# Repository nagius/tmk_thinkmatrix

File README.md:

# ThinkMatrix Keyboard Firmware

This is the firmware for my custom ortholinear keyboard, based on the [tmk keyboard library](https://github.com/tmk/tmk_core).  

The keyboard runs on a [Teensy 2.0](http://www.pjrc.com/store/teensy.html). You can find more detail about the design of keyboard itself in the directory `docs`.

Images and a buildlog of the keyboard can be found [here](https://geekhack.org/index.php?topic=76167.0).

## Cloning, building & flashing

You need the AVR cross-compilation toolstack to compile the firmware.

See [tmk keyboard](https://github.com/tmk/tmk_keyboard) and [Teensy howto](https://www.pjrc.com/teensy/gcc.html) for more informations.

Since this repository has a submodule the cloning needs an additional argument to init and update the submodule.

```
git clone --recursive https://github.com/nagius/tmk_thinkmatrix
cd tmk_thinkmatrix
make
```

This will generate the firmware file `thinkmatrix-fw.hex`.

### Upload

Start the graphical [loader tool](https://www.pjrc.com/teensy/loader_linux.html) :

```
teensy.64bit &
```

Plug the Teensy on USB, push the program button, select the generated file `thinkmatrix-fw.hex` and click 'Upload'.

## Update to the lastest version

```
git pull
git submodule sync --recursive
git submodule update --init --recursive
```

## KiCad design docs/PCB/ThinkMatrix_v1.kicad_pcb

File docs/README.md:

# Documentation, schematics and drawing

You will find in this directory the files needed to buid the keyboard. Everything is released under GNU/GPLv3 Licence if not specified otherwise.
 
 - keyboard-layout.json: Data file for http://www.keyboard-layout-editor.com/
 - CAD: All LibreCAD needed to build the case and the plate
 - PCB: the KiCad project to make the PCB

Please note there is a couple of errors on this PCB design:

 - The pins labelling of the Teensy module are wrong, please refer to the table below for the correct pinout.
 - When soldering the Teensy, pins C6 and D7 must be swapped (with a couple of wire for example).
 - Clearance around the Cherry MX stabilizers is not good enough in few cases, 5 of the resistors need to be soldiered on the back of the board.
 - The diodes are in the wrong way around for the tmk_keyboard firmware, the matrix need to be rotated in the source code. Note this is tmk specific, it does not apply if you're using a qmk_keyboard firmware.

## Teensy pinout

 - Matrix

| Row | 0  | 1  | 2  | 3  | 4  | 5  | 6  |
|-----|----|----|----|----|----|----|----|
| Pin | B2 | B0 | B1 | E6 | B3 | B7 | D0 |

| Col | 0  | 1  | 2  | 3  | 4  | 5  | 6  | 7  | 8  | 9  | 10 | 11 | 12 | 13 |
|-----|----|----|----|----|----|----|----|----|----|----|----|----|----|----|
| Pin | F0 | F1 | F4 | B4 | F5 | D3 | D2 | C7 | F7 | B6 | B5 | D5 | D4 | C6 |

 - Front leds: D1, D6, F6
 - Backlight: D7

## Parts list

 - 1x  Teensy 2.0
 - 85x Cherry MX switches
 - 9x  Cherry MX stabilizers
 - 85x Diodes 1N4148
 - 89x Orange LEDs (1.92V @ 7mA)
 - 43x Resistors 36 ohms
 - 4x  Resistors 200 ohms
 - 1x  Resistor 1.4k ohms
 - 1x  Capacitor 100µF
 - 1x  Transistor 2N3904
 - 1x  Transistor PN2907A

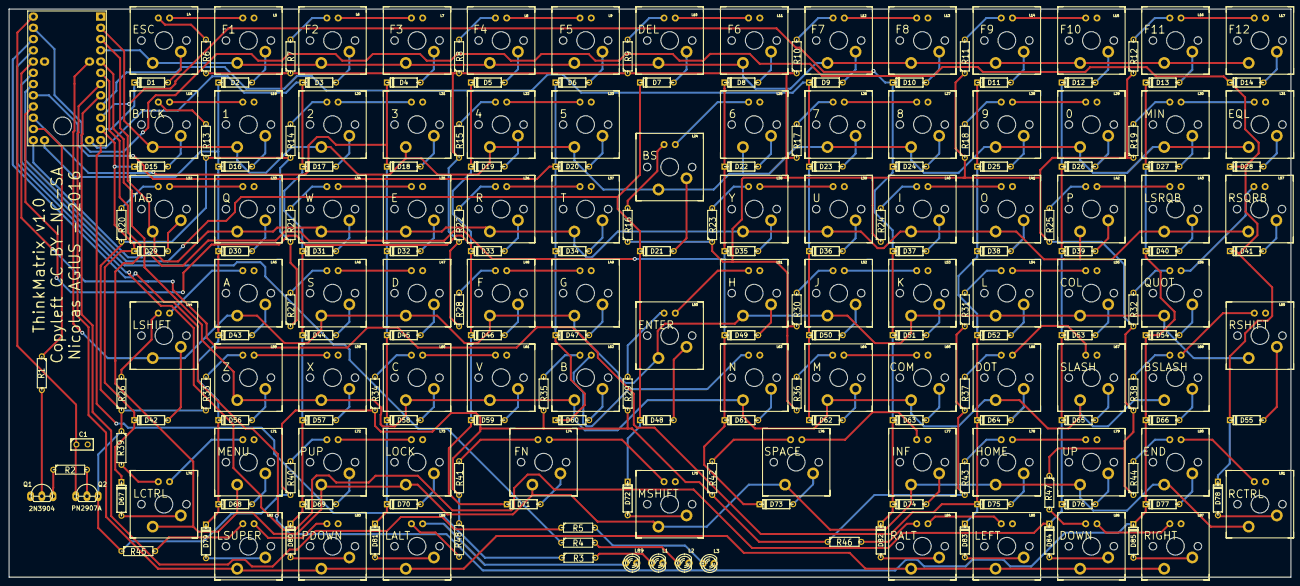
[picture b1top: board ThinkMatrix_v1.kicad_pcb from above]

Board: 2 copper layers, 289.7 x 128.4 mm, 311 parts (0 on the bottom side), 205 nets.

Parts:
C1: 47µF; C1
D1, D2, D3, D4, D5, D6, D7, D8, D9, D10, D11, D12, D13, D14, D15, D16, D17, D18, D19, D20, D21, D22, D23, D24, D25, D26, D27, D28, D29, D30, D31, D32, D33, D34, D35, D36, D37, D38, D39, D40, D41, D42, D43, D44, D45, D46, D47, D48, D49, D50, D51, D52, D53, D54, D55, D56, D57, D58, D59, D60, D61, D62, D63, D64, D65, D66, D67, D68, D69, D70, D71, D72, D73, D74, D75, D76, D77, D78, D79, D80, D81, D82, D83, D84, D85: DIODE; D3
L1, L2, L3, L89: LED-3MM
L4: L4; MX1A-led-rev
L5: L5; MX1A-led-rev
L6: L6; MX1A-led-rev
L7: L7; MX1A-led-rev
L8: L8; MX1A-led-rev
L9: L9; MX1A-led-rev
L10: L10; MX1A-led-rev
L11: L11; MX1A-led-rev
L12: L12; MX1A-led-rev
L13: L13; MX1A-led-rev
L14: L14; MX1A-led-rev
L15: L15; MX1A-led-rev
L16: L16; MX1A-led-rev
L17: L17; MX1A-led-rev
L18: L18; MX1A-led-rev
L19: L19; MX1A-led-rev
L20: L20; MX1A-led-rev
L21: L21; MX1A-led-rev
L22: L22; MX1A-led-rev
L23: L23; MX1A-led-rev
L24: L24; MX1A-led-rev
L25: L25; MX1A-led-rev
L26: L26; MX1A-led-rev
L27: L27; MX1A-led-rev
L28: L28; MX1A-led-rev
L29: L29; MX1A-led-rev
L30: L30; MX1A-led-rev
L31: L31; MX1A-led-rev
L32: L32; MX1A-led-rev
L33: L33; MX1A-led-rev
L34: L34; MX1A-led-rev
L35: L35; MX1A-led-rev
L36: L36; MX1A-led-rev
L37: L37; MX1A-led-rev
L38: L38; MX1A-led-rev
L39: L39; MX1A-led-rev
L40: L40; MX1A-led-rev
L41: L41; MX1A-led-rev
L42: L42; MX1A-led-rev
L43: L43; MX1A-led-rev
L44: L44; MX1A-led-rev
L45: L45; MX1A-led-rev
L46: L46; MX1A-led-rev
L47: L47; MX1A-led-rev
L48: L48; MX1A-led-rev
L49: L49; MX1A-led-rev
L50: L50; MX1A-led-rev
L51: L51; MX1A-led-rev
L52: L52; MX1A-led-rev
L53: L53; MX1A-led-rev
L54: L54; MX1A-led-rev
L55: L55; MX1A-led-rev
L56: L56; MX1A-led-rev
L57: L57; MX1A-led-rev
L58: L58; MX1A-led-rev
L59: L59; MX1A-led-rev
L60: L60; MX1A-led-rev
L61: L61; MX1A-led-rev
L62: L62; MX1A-led-rev
L63: L63; MX1A-led-rev
L64: L64; MX1A-led-rev
L65: L65; MX1A-led-rev
L66: L66; MX1A-led-rev
L67: L67; MX1A-led-rev
L68: L68; MX1A-led-rev
L69: L69; MX1A-led-rev
L70: L70; MX1A-led-rev
L71: L71; MX1A-led-rev
L72: L72; MX1A-led-rev
L73: L73; MX1A-led-rev
L74: L74; MX1A-led-rev
L75: L75; MX1A-led-rev
L76: L76; MX1A-led-rev
L77: L77; MX1A-led-rev
L78: L78; MX1A-led-rev
L79: L79; MX1A-led-rev
L80: L80; MX1A-led-rev
L81: L81; MX1A-led-rev
L82: L82; MX1A-led-rev
L83: L83; MX1A-led-rev
L84: L84; MX1A-led-rev
L85: L85; MX1A-led-rev
L86: L86; MX1A-led-rev
L87: L87; MX1A-led-rev
L88: L88; MX1A-led-rev
Q1: 2N3904; LV_TO92-123_oval
Q2: PN2907A; LV_TO92-123_oval
R1: R1; R3
R2: R2; R3
R3: R3
R4: R4; R3
R5: R5; R3
R6: R6; R3
R7: R7; R3
R8: R8; R3
R9: R9; R3
R10: R10; R3
R11: R11; R3
R12: R12; R3
R13: R13; R3
R14: R14; R3
R15: R15; R3
R16: R16; R3
R17: R17; R3
R18: R18; R3
R19: R19; R3
R20: R20; R3
R21: R21; R3
R22: R22; R3
R23: R23; R3
R24: R24; R3
R25: R25; R3
R26: R26; R3
R27: R27; R3
R28: R28; R3
R29: R29; R3
R30: R30; R3
R31: R31; R3
R32: R32; R3
R33: R33; R3
R34: R34; R3
R35: R35; R3
R36: R36; R3
R37: R37; R3
R38: R38; R3
R39: R39; R3
R40: R40; R3
R41: R41; R3
R42: R42; R3
R43: R43; R3
R44: R44; R3
R45: R45; R3
R46: R46; R3
R47: R47; R3
R48: R48; R3
SW0:0: ESC; SW_PCB_2PIN_NO
SW0:1: F1; SW_PCB_2PIN_NO
SW0:2: F2; SW_PCB_2PIN_NO
SW0:3: F3; SW_PCB_2PIN_NO
SW0:4: F4; SW_PCB_2PIN_NO
SW0:5: F5; SW_PCB_2PIN_NO
SW0:6: DEL; SW_PCB_2PIN_NO
SW0:7: F6; SW_PCB_2PIN_NO
SW0:8: F7; SW_PCB_2PIN_NO
SW0:9: F8; SW_PCB_2PIN_NO
SW0:10: F9; SW_PCB_2PIN_NO
SW0:11: F10; SW_PCB_2PIN_NO
SW0:12: F11; SW_PCB_2PIN_NO
SW0:13: F12; SW_PCB_2PIN_NO
SW1:0: BTICK; SW_PCB_2PIN_NO
SW1:1: 1; SW_PCB_2PIN_NO
SW1:2: 2; SW_PCB_2PIN_NO
SW1:3: 3; SW_PCB_2PIN_NO
SW1:4: 4; SW_PCB_2PIN_NO
SW1:5: 5; SW_PCB_2PIN_NO
SW1:6: BS; SW_PCB_2PIN_NO
SW1:7: 6; SW_PCB_2PIN_NO
SW1:8: 7; SW_PCB_2PIN_NO
SW1:9: 8; SW_PCB_2PIN_NO
SW1:10: 9; SW_PCB_2PIN_NO
SW1:11: 0; SW_PCB_2PIN_NO
SW1:12: MIN; SW_PCB_2PIN_NO
SW1:13: EQL; SW_PCB_2PIN_NO
SW2:0: TAB; SW_PCB_2PIN_NO
SW2:1: Q; SW_PCB_2PIN_NO
SW2:2: W; SW_PCB_2PIN_NO
SW2:3: E; SW_PCB_2PIN_NO
SW2:4: R; SW_PCB_2PIN_NO
SW2:5: T; SW_PCB_2PIN_NO
SW2:7: Y; SW_PCB_2PIN_NO
SW2:8: U; SW_PCB_2PIN_NO
SW2:9: I; SW_PCB_2PIN_NO
SW2:10: O; SW_PCB_2PIN_NO
SW2:11: P; SW_PCB_2PIN_NO
SW2:12: LSRQB; SW_PCB_2PIN_NO
SW2:13: RSQRB; SW_PCB_2PIN_NO
SW3:0: LSHIFT; SW_PCB_2PIN_NO
SW3:1: A; SW_PCB_2PIN_NO
SW3:2: S; SW_PCB_2PIN_NO
SW3:3: D; SW_PCB_2PIN_NO
SW3:4: F; SW_PCB_2PIN_NO
SW3:5: G; SW_PCB_2PIN_NO
SW3:6: ENTER; SW_PCB_2PIN_NO
SW3:7: H; SW_PCB_2PIN_NO
SW3:8: J; SW_PCB_2PIN_NO
SW3:9: K; SW_PCB_2PIN_NO
SW3:10: L; SW_PCB_2PIN_NO
SW3:11: COL; SW_PCB_2PIN_NO
SW3:12: QUOT; SW_PCB_2PIN_NO
SW3:13: RSHIFT; SW_PCB_2PIN_NO
SW4:1: Z; SW_PCB_2PIN_NO
SW4:2: X; SW_PCB_2PIN_NO
SW4:3: C; SW_PCB_2PIN_NO
SW4:4: V; SW_PCB_2PIN_NO
SW4:5: B; SW_PCB_2PIN_NO
SW4:7: N; SW_PCB_2PIN_NO
SW4:8: M; SW_PCB_2PIN_NO
SW4:9: COM; SW_PCB_2PIN_NO
SW4:10: DOT; SW_PCB_2PIN_NO
SW4:11: SLASH; SW_PCB_2PIN_NO
SW4:12: BSLASH; SW_PCB_2PIN_NO
SW5:0: LCTRL; SW_PCB_2PIN_NO
SW5:1: MENU; SW_PCB_2PIN_NO
SW5:2: PUP; SW_PCB_2PIN_NO
SW5:3: LOCK; SW_PCB_2PIN_NO
SW5:4: FN; SW_PCB_2PIN_NO
SW5:6: MSHIFT; SW_PCB_2PIN_NO
SW5:7: SPACE; SW_PCB_2PIN_NO
SW5:9: INF; SW_PCB_2PIN_NO
SW5:10: HOME; SW_PCB_2PIN_NO
SW5:11: UP; SW_PCB_2PIN_NO
SW5:12: END; SW_PCB_2PIN_NO
SW5:13: RCTRL; SW_PCB_2PIN_NO
SW6:1: LSUPER; SW_PCB_2PIN_NO
SW6:2: PDOWN; SW_PCB_2PIN_NO
SW6:3: LALT; SW_PCB_2PIN_NO
SW6:9: RALT; SW_PCB_2PIN_NO
SW6:10: LEFT; SW_PCB_2PIN_NO
SW6:11: DOWN; SW_PCB_2PIN_NO
SW6:12: RIGHT; SW_PCB_2PIN_NO
U1: TEENSY2.0; TEENSY_2.0_rev

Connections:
GND: C1.2, L1.2, L2.2, L3.2, L5.2, L7.2, L9.2, L11.2, L13.2, L15.2, L17.2, L19.2, L21.2, L23.2, L25.2, L27.2, L29.2, L31.2, L33.2, L35.2, L37.2, L39.2, L41.2, L43.2, L45.2, L47.2, L49.2, L51.2, L53.2, L55.2, L57.2, L59.2, L61.2, L63.2, L65.2, L67.2, L69.2, L71.2, L73.2, L75.2, L77.2, L79.2, L81.2, L83.2, L85.2, L87.2, L89.2, Q1.1, U1.1
unnamed: L34.1, R21.2
unnamed: L36.1, R22.2
unnamed: L36.2, L37.1
unnamed: L34.2, L35.1
unnamed: L32.2, L33.1
unnamed: L32.1, R20.2
unnamed: L38.1, R23.2
unnamed: L40.1, R24.2
unnamed: L40.2, L41.1
unnamed: L38.2, L39.1
unnamed: L28.1, R18.2
unnamed: L28.2, L29.1
unnamed: L26.2, L27.1
unnamed: L26.1, R17.2
unnamed: L24.2, L25.1
unnamed: L24.1, R16.2
unnamed: L30.2, L31.1
unnamed: L30.1, R19.2
unnamed: L52.1, R30.2
unnamed: L54.1, R31.2
unnamed: L52.2, L53.1
unnamed: L54.2, L55.1
unnamed: L50.2, L51.1
unnamed: L50.1, R29.2
unnamed: L56.2, L57.1
unnamed: L58.1, R33.2
unnamed: L58.2, L59.1
unnamed: L56.1, R32.2
unnamed: L44.2, L45.1
unnamed: L44.1, R26.2
unnamed: L46.2, L47.1
unnamed: L42.2, L43.1
unnamed: L42.1, R25.2
unnamed: L48.2, L49.1
unnamed: L48.1, R28.2
unnamed: L46.1, R27.2
unnamed: R1.1, U1.19
unnamed: Q1.3, R2.1
unnamed: Q2.2, R2.2
unnamed: Q1.2, R1.2
unnamed: L6.1, R7.2
unnamed: L6.2, L7.1
unnamed: R4.1, U1.24
unnamed: R5.1, U1.8
unnamed: R3.1, U1.12
unnamed: L4.2, L5.1
unnamed: L20.2, L21.1
unnamed: L18.2, L19.1
unnamed: L18.1, R13.2
unnamed: L20.1, R14.2
unnamed: L16.2, L17.1
unnamed: L16.1, R12.2
unnamed: L22.1, R15.2
unnamed: L22.2, L23.1
unnamed: L8.2, L9.1
unnamed: L10.2, L11.1
unnamed: L10.1, R9.2
unnamed: L8.1, R8.2
unnamed: L14.2, L15.1
unnamed: L14.1, R11.2
unnamed: L12.2, L13.1
unnamed: L12.1, R10.2
unnamed: SW2:0.1, SW2:1.1, SW2:2.1, SW2:3.1, SW2:4.1, SW2:5.1, SW2:7.1, SW2:8.1, SW2:9.1, SW2:10.1, SW2:11.1, SW2:12.1, SW2:13.1, U1.3
unnamed: D12.2, D26.2, D39.2, D53.2, D65.2, D76.2, D84.2, U1.26
unnamed: L68.1, R38.2
unnamed: L70.1, R39.2
unnamed: L70.2, L71.1
unnamed: L68.2, L69.1
unnamed: L66.2, L67.1
unnamed: L66.1, R37.2
unnamed: L72.2, L73.1
unnamed: L74.2, L75.1
unnamed: L74.1, R41.2
unnamed: L72.1, R40.2
unnamed: L62.1, R35.2
unnamed: L62.2, L63.1
unnamed: L60.2, L61.1
unnamed: L60.1, R34.2
unnamed: L64.2, L65.1
unnamed: L64.1, R36.2
unnamed: L86.1, R47.2
unnamed: L88.1, R48.2
unnamed: L86.2, L87.1
unnamed: L88.2, L89.1
unnamed: L84.2, L85.1
unnamed: L84.1, R46.2
unnamed: D1.2, D15.2, D29.2, D42.2, D67.2, U1.11
unnamed: D6.2, D20.2, D34.2, D47.2, D60.2, U1.22
unnamed: D7.2, D21.2, D48.2, D72.2, U1.23
unnamed: L78.2, L79.1
unnamed: L78.1, R43.2
unnamed: L80.2, L81.1
unnamed: L76.2, L77.1
unnamed: L76.1, R42.2
unnamed: L82.2, L83.1
unnamed: L82.1, R45.2
unnamed: L4.1, R6.2
unnamed: L80.1, R44.2
unnamed: Q2.3, R6.1, R7.1, R8.1, R9.1, R10.1, R11.1, R12.1, R13.1, R14.1, R15.1, R16.1, R17.1, R18.1, R19.1, R20.1, R21.1, R22.1, R23.1, R24.1, R25.1, R26.1, R27.1, R28.1, R29.1, R30.1, R31.1, R32.1, R33.1, R34.1, R35.1, R36.1, R37.1, R38.1, R39.1, R40.1, R41.1, R42.1, R43.1, R44.1, R45.1, R46.1, R47.1, R48.1
unnamed: D46.1, SW3:4.2
unnamed: D33.1, SW2:4.2
unnamed: D5.2, D19.2, D33.2, D46.2, D59.2, D71.2, U1.21
unnamed: D19.1, SW1:4.2
unnamed: D4.1, SW0:3.2
unnamed: D71.1, SW5:4.2
unnamed: D59.1, SW4:4.2
unnamed: D4.2, D18.2, D32.2, D45.2, D58.2, D70.2, D81.2, U1.20
unnamed: D58.1, SW4:3.2
unnamed: D45.1, SW3:3.2
unnamed: D32.1, SW2:3.2
unnamed: D18.1, SW1:3.2
unnamed: D81.1, SW6:3.2
unnamed: D5.1, SW0:4.2
unnamed: D70.1, SW5:3.2
unnamed: D48.1, SW3:6.2
unnamed: D72.1, SW5:6.2
unnamed: D21.1, SW1:6.2
unnamed: D35.1, SW2:7.2
unnamed: D22.1, SW1:7.2
unnamed: D7.1, SW0:6.2
unnamed: D20.1, SW1:5.2
unnamed: D34.1, SW2:5.2
unnamed: D60.1, SW4:5.2
unnamed: D6.1, SW0:5.2
unnamed: D47.1, SW3:5.2
unnamed: D67.1, SW5:0.2
unnamed: D1.1, SW0:0.2
unnamed: SW1:0.1, SW1:1.1, SW1:2.1, SW1:3.1, SW1:4.1, SW1:5.1, SW1:6.1, SW1:7.1, SW1:8.1, SW1:9.1, SW1:10.1, SW1:11.1, SW1:12.1, SW1:13.1, U1.2
unnamed: D42.1, SW3:0.2
unnamed: D43.1, SW3:1.2
unnamed: D30.1, SW2:1.2
unnamed: D16.1, SW1:1.2
unnamed: D15.1, SW1:0.2
unnamed: D29.1, SW2:0.2
unnamed: C1.1, Q2.1, U1.29
unnamed: D3.2, D17.2, D31.2, D44.2, D57.2, D69.2, D80.2, U1.13
unnamed: D69.1, SW5:2.2
unnamed: D57.1, SW4:2.2
unnamed: D44.1, SW3:2.2
unnamed: D3.1, SW0:2.2
unnamed: D31.1, SW2:2.2
unnamed: D80.1, SW6:2.2
unnamed: D68.1, SW5:1.2
unnamed: D79.1, SW6:1.2
unnamed: D2.2, D16.2, D30.2, D43.2, D56.2, D68.2, D79.2, U1.17
unnamed: D56.1, SW4:1.2
unnamed: D17.1, SW1:2.2
unnamed: D2.1, SW0:1.2
unnamed: D27.1, SW1:12.2
unnamed: D40.1, SW2:12.2
unnamed: D12.1, SW0:11.2
unnamed: D66.1, SW4:12.2
unnamed: D77.1, SW5:12.2
unnamed: D54.1, SW3:12.2
unnamed: SW4:1.1, SW4:2.1, SW4:3.1, SW4:4.1, SW4:5.1, SW4:7.1, SW4:8.1, SW4:9.1, SW4:10.1, SW4:11.1, SW4:12.1, U1.5
unnamed: D53.1, SW3:11.2
unnamed: D65.1, SW4:11.2
unnamed: D39.1, SW2:11.2
unnamed: D26.1, SW1:11.2
unnamed: D76.1, SW5:11.2
unnamed: D84.1, SW6:11.2
unnamed: L1.1, R3.2
unnamed: L2.1, R4.2
unnamed: D14.1, SW0:13.2
unnamed: L3.1, R5.2
unnamed: D13.2, D27.2, D40.2, D54.2, D66.2, D77.2, D85.2, U1.27
unnamed: D28.1, SW1:13.2
unnamed: D14.2, D28.2, D41.2, D55.2, D78.2, U1.28
unnamed: D13.1, SW0:12.2
unnamed: D85.1, SW6:12.2
unnamed: D55.1, SW3:13.2
unnamed: D78.1, SW5:13.2
unnamed: D41.1, SW2:13.2
unnamed: D62.1, SW4:8.2
unnamed: D9.1, SW0:8.2
unnamed: D9.2, D23.2, D36.2, D50.2, D62.2, U1.9
unnamed: SW0:0.1, SW0:1.1, SW0:2.1, SW0:3.1, SW0:4.1, SW0:5.1, SW0:6.1, SW0:7.1, SW0:8.1, SW0:9.1, SW0:10.1, SW0:11.1, SW0:12.1, SW0:13.1, U1.4
unnamed: D50.1, SW3:8.2
unnamed: D51.1, SW3:9.2
unnamed: SW3:0.1, SW3:1.1, SW3:2.1, SW3:3.1, SW3:4.1, SW3:5.1, SW3:6.1, SW3:7.1, SW3:8.1, SW3:9.1, SW3:10.1, SW3:11.1, SW3:12.1, SW3:13.1, U1.31
unnamed: D37.1, SW2:9.2
unnamed: D24.1, SW1:9.2
unnamed: D73.1, SW5:7.2
unnamed: D8.2, D22.2, D35.2, D49.2, D61.2, D73.2, U1.18
unnamed: D61.1, SW4:7.2
unnamed: D49.1, SW3:7.2
unnamed: D23.1, SW1:8.2
unnamed: D36.1, SW2:8.2
unnamed: D8.1, SW0:7.2
unnamed: D75.1, SW5:10.2
unnamed: D64.1, SW4:10.2
unnamed: D11.2, D25.2, D38.2, D52.2, D64.2, D75.2, D83.2, U1.25
unnamed: D52.1, SW3:10.2
unnamed: D38.1, SW2:10.2
unnamed: D11.1, SW0:10.2
unnamed: D83.1, SW6:10.2
unnamed: SW5:0.1, SW5:1.1, SW5:2.1, SW5:3.1, SW5:4.1, SW5:6.1, SW5:7.1, SW5:9.1, SW5:10.1, SW5:11.1, SW5:12.1, SW5:13.1, U1.6
unnamed: D10.2, D24.2, D37.2, D51.2, D63.2, D74.2, D82.2, U1.10
unnamed: D82.1, SW6:9.2
unnamed: SW6:1.1, SW6:2.1, SW6:3.1, SW6:9.1, SW6:10.1, SW6:11.1, SW6:12.1, U1.7
unnamed: D74.1, SW5:9.2
unnamed: D63.1, SW4:9.2
unnamed: D25.1, SW1:10.2
unnamed: D10.1, SW0:9.2

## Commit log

2016-10-15 Added tmk_core submodule
2016-10-15 Added source code
2016-10-15 Added comments
2016-10-15 Added init_leds() function
2016-10-15 Updated gitignore
2016-10-16 Added readme
2016-10-16 Added docs
2016-10-16 Fix docs formatting
2017-04-02 Updated tmk_core submodule
2017-04-02 Updated doc
2017-04-08 Replaced Tab by Backspace in Fn layer
2017-04-08 Updated pinout for version 2
2017-04-08 Added PMW on front leds

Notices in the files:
docs/PCB/ThinkMatrix_v1.kicad_pcb:
Copyleft CC BY-NC-SA
